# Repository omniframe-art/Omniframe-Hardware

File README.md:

**Omniframe Hardware**

Omniframe is an open source e-paper digital frame. This repository includes the source and fabrication files for the main and secondary boards for driving the [13.3" Monochrome e-ink display](https://www.eink.com/product/detail/VB3300-NCB).

Main Board includes:
* ESP32-S3 N8R2
* TPS65185
* AP61100
* BQ25505
* BQ24040
* MicroSD card slot

Secondary Board includes:
* USB Type-C Port
* Pushbutton connected to ESP GPIO

Exports include:
* Gerber files
* Assembly files
* BOM
* STEP files

The main board includes Molex 5023520-series connectors for Solar Array, Battery, and and Secondary Board. By default, connecting the main and secondary boards is done with a ribbon cable with [Molex 5023510500](https://www.digikey.com/en/products/detail/molex/5023510500/4555379) housings. Alternatively, the source files can be modified to accomodate for other connectors. 

To operate the e-paper display using this hardware, flash the [Omniframe Firmware](https://github.com/omniframe-art/Omniframe-Firmware) to the ESP. For converting and transferring images set up the [Private Image Server](https://github.com/omniframe-art/Private-Image-Server).

**Licensing**

The Omniframe framework is licensed under the terms of the [Creative Commons Attribution-ShareAlike 4.0 International License](https://creativecommons.org/licenses/by-sa/4.0/).

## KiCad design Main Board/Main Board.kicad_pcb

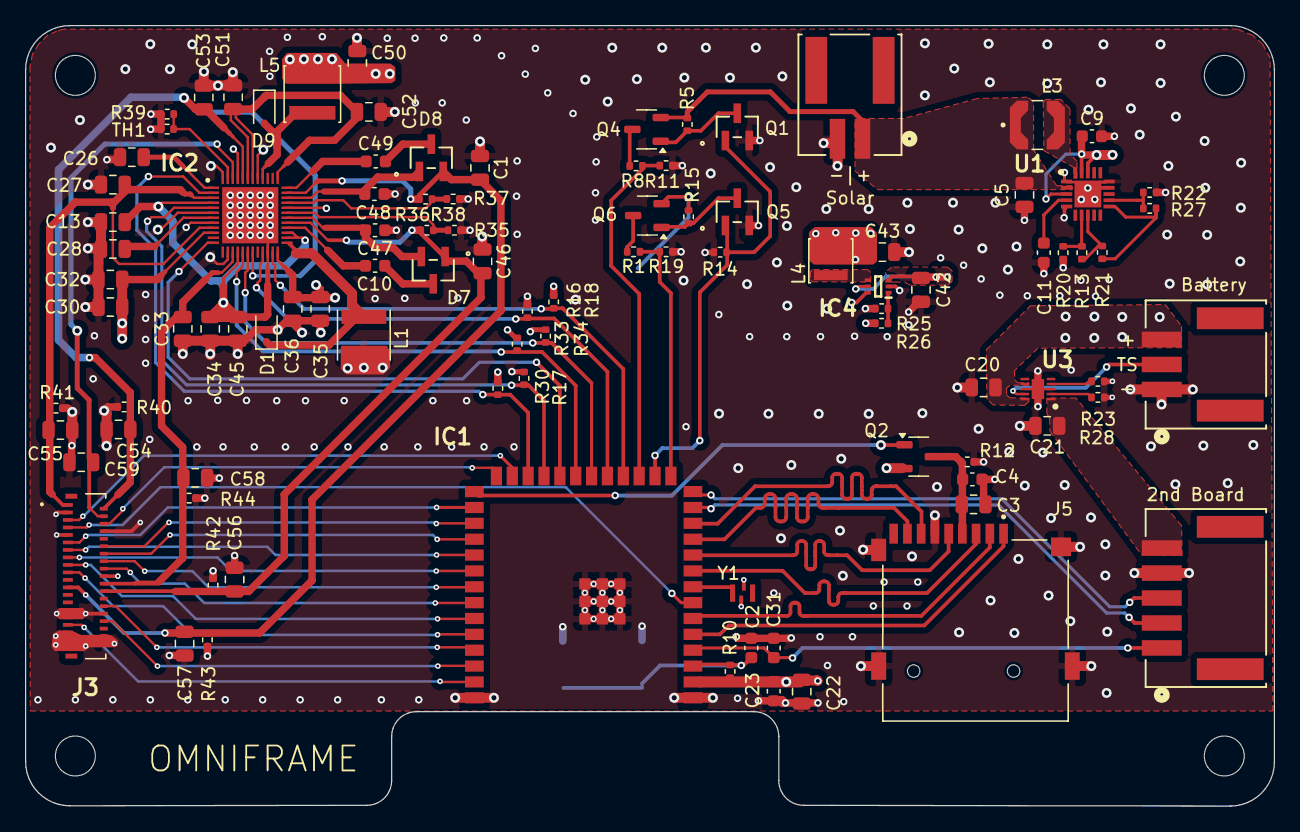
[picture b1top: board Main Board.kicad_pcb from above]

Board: 4 copper layers, 100.0 x 62.5 mm, 104 parts (1 on the bottom side), 79 nets.

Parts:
C1, C46: 2u2; C_0805_2012Metric
C2, C4, C22, C31, C47, C48: 100n; C_0603_1608Metric
C3, C23, C32, C36, C42: 22u; C_0805_2012Metric
C5, C13, C26, C27, C28, C33, C34, C45, C51, C52, C53: 4u7; C_0805_2012Metric
C9, C10, C11, C49: 10n; C_0603_1608Metric
C20, C21: 1u; C_0805_2012Metric
C30, C35, C43, C50, C59: 10u; C_0805_2012Metric
C54, C55, C58: 1uF/25V; C_0805_2012Metric
C56, C57: 1uF/50V; C_0805_2012Metric
D1, D9: BAS3010B-03W; D_SOD-323
D7, D8: BAV99,215; SOT-23TO-236_318-08_ONS-M
H1, H2, H3, H4: MountingHole; MountingHole_3.2mm_M3
IC1: ESP32-S3-WROOM-1-N8R2; ESP32S3WROOM1N8R2
IC2: TPS65185RSLT; QFN40P600X600X100-49N-D
IC4: AP61100; SOTFL50P162X60-6N
J2: 5023520300; CONN03_502352_MOL
J3: FH26W-39S-0.3SHW(60); FH26W39S03SHW60
J4: 5023520500; CONN05_502352_MOL
J5: MSD-1-A; CUI_MSD-1-A
J6: 5023520200; CONN02_502352_MOL
L1: 4.7uH 2A; L_Vishay_IFSC-1515AH_4x4x1.8mm
L3: LPS4018-223MRC; IND_LPS4018-223MRC
L4: NRH3012T1R0NN; L_Changjiang_FNR3012S
L5: 2.2uH 2A; L_Changjiang_FNR4012S
Q1, Q5: 2N7002; SOT-23TO-236_318-08_ONS-M
Q2, Q4, Q6: BSS84-7-F; SOT-23-3
R1, R5, R8, R15, R16, R17, R18, R30, R33, R34: 10k; R_0402_1005Metric
R10, R12, R14, R40, R41, R42, R43: 47k; R_0402_1005Metric
R11, R19: 30k; R_0402_1005Metric
R13: 7M32; R_0402_1005Metric
R20: 5M62; R_0402_1005Metric
R21: 1M1; R_0402_1005Metric
R22: 7M68; R_0402_1005Metric
R23: 2k; R_0402_1005Metric
R25: 44k2; R_0402_1005Metric
R26: 200k; R_0402_1005Metric
R27: 4M22; R_0402_1005Metric
R28: 590; R_0402_1005Metric
R35: 52k3; R_0402_1005Metric
R36, R38: 1M; R_0402_1005Metric
R37: 41k6; R_0402_1005Metric
R39: 43k; R_0402_1005Metric
R44: 100k; R_0402_1005Metric
S1: TS5216A 160gf 025; TS18525SL260SMTTR
TH1: 10k/3380K; R_0402_1005Metric
U1: BQ25505; QFN50P350X350X100-21N-D
U3: BQ24040DSQR; SON40P200X200X80-11N
Y1: SIT1533AC-H4-DCC-32.768E; XTAL4_SiT1533_SIT

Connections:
3V3: C22.1, C23.1, C43.1, IC1.2 (3V3), IC2.45 (VIN3P3), IC4.6 (OUT), L4.2, Q2.2 (S), R10.2, R18.2, R26.2, R30.2, R33.2, R34.2, Y1.4 (Vdd)
/15V: C53.2, C54.2, IC2.19 (VPOS_DIS), IC2.44 (VPOS), J3.2, R40.2
/22V: C1.2, C57.2, D8.2, IC2.35 (VDDH_DIS), J3.23, R38.1, R43.2
/32KP: IC1.8 (IO15), Y1.3 (CLK_Out)
/-15V: C27.1, C55.2, IC2.3 (VNEG), IC2.9 (VNEG_DIS), J3.1, R41.2
/-20V: C46.2, C56.2, D7.1, IC2.29 (VEE_DIS), J3.24, R36.1, R42.2
/BAT_VOL: IC1.15 (IO3), R1.1, R19.2
/CKV: IC1.39 (IO1), J3.33
/D0: IC1.29 (IO36), J3.12
/D1: IC1.31 (IO38), J3.13
/D2: IC1.30 (IO37), J3.14
/D3: IC1.32 (IO39), J3.15
/D4: IC1.33 (IO40), J3.16
/D5: IC1.35 (IO42), J3.17
/D6: IC1.34 (IO41), J3.18
/D7: IC1.36 (RXD0), J3.19
/EN: C2.1, IC1.3 (EN), R10.1, S1.1 (NO_1), S1.2 (NO_2)
/EPD_VDD: C59.1, IC2.46 (V3P3), J3.4
/FB: IC4.1 (FB), R25.2, R26.1
/INT_LDO: C28.2, IC2.7 (INT_LDO)
/ISET: R28.2, U3.2 (ISET)
/MODE1: IC1.37 (TXD0), J3.28
/PRE-T: R23.2, U3.4 (PRE-TERM)
/PWRUP: IC1.19 (IO11), IC2.21 (PWRUP), R16.2
/PWR_G: IC1.18 (IO10), IC2.23 (PWR_GOOD), R18.1
/SCL: IC1.21 (IO13), IC2.17 (SCL), R33.1
/SDA: IC1.20 (IO12), IC2.18 (SDA), R34.1
/SD_CLK: IC1.10 (IO17), J5.5 (CLK)
/SD_CMD: IC1.9 (IO16), J5.3 (CMD)
/SD_D0: IC1.12 (IO8), J5.7 (DAT0)
/SD_D1: IC1.11 (IO18), J5.8 (DAT1)
/SD_D2: IC1.5 (IO5), J5.1 (DAT2)
/SD_D3: IC1.6 (IO6), J5.2 (CD/DAT3)
/SD_EN: IC1.27 (IO0), Q2.1 (G)
/SIG: C31.1, IC1.4 (IO4), J4.1
/SOL+: C5.1, J6.1, L3.1, Q4.2 (S), R5.2, U1.2 (VIN_DC)
/SOL_VOL: IC1.17 (IO9), R8.1, R11.2
/SPV: IC1.38 (IO2), J3.32
/SW: IC4.4 (SW), L4.1
/TS: J2.2, U3.9 (TS)
/USB_N: IC1.13 (IO19), J4.2
/USB_P: IC1.14 (IO20), J4.3
/VBAT: C9.1, C20.1, C30.1, C32.2, C35.1, C36.2, C42.1, C50.1, IC2.10 (VIN), IC2.24 (VIN_P), IC4.3 (VIN), IC4.5 (EN), J2.3, L5.2, Q6.2 (S), R15.2, U1.3 (VOC_SAMP), U1.18 (VBAT_SEC), U1.19 (VSTOR), U3.7 (ISET2), U3.10 (OUT)
/VBUS: C21.1, J4.5, U3.1 (IN)
/VCOM: C33.2, C58.2, IC2.15 (VCOM), J3.22, R44.2
/VCTRL: IC1.22 (IO14), IC2.12 (VCOM_CTRL)
/VDDH_D: C48.1, D8.1, IC2.34 (VDDH_D)
/VDDH_DRV: C49.1, IC2.36 (VDDH_DRV)
/VDDH_FB: IC2.33 (VDDH_FB), R37.2, R38.2
/VEE_D: C47.2, D7.2, IC2.30 (VEE_D)
/VEE_DRV: C10.1, IC2.28 (VEE_DRV)
/VEE_FB: IC2.31 (VEE_FB), R35.2, R36.2
/VNEG_IN: C13.1, C34.1, C45.2, D1.2 (A), IC2.4 (VNEG_IN), IC2.16 (VCOM_PWR), IC2.22 (PBKG), IC2.26 (VN), IC2.27 (VEE_IN), IC2.49 (EP)
/VN_SW: D1.1 (K), IC2.25 (VN_SW), L1.1
/VOL_EN: IC1.16 (IO46), Q1.1 (G), Q5.1 (G), R14.2
/VREF: C26.2, IC2.1 (VREF)
/WKUP: IC1.23 (IO21), IC2.5 (WAKEUP), R17.2
/XCL: IC1.25 (IO48), J3.5
/XLE: IC1.26 (IO45), J3.6
/XOE: IC1.7 (IO7), J3.7
/XSTL: IC1.28 (IO35), J3.11
/nINT: IC1.24 (IO47), IC2.2 (~INT), R30.1
GND: C1.1, C2.2, C3.2, C4.2, C5.2, C9.2, C11.2, C13.2, C20.2, C21.2, C22.2, C23.2, C26.1, C27.2, C28.1, C30.2, C31.2, C32.1, C33.1, C34.2, C35.2, C36.1, C42.2, C43.2, C45.1, C46.1, C47.1, C48.2, C50.2, C51.1, C52.1, C53.1, C54.1, C55.1, C56.1, C57.1, C58.1, C59.2, IC1.1 (GND_1), IC1.40 (GND_2), IC1.41 (GND_3), IC1.42 (GND_4), IC1.43 (GND_5), IC1.44 (GND_6), IC1.45 (GND_7), IC1.46 (GND_8), IC1.47 (GND_9), IC1.48 (GND_10), IC1.49 (GND_11), IC2.6 (DGND), IC2.8 (AGND1), IC2.14 (VCOM_DIS), IC2.32 (PGND2), IC2.41 (PGND1), IC2.48 (AGND2), IC4.2 (GND), J2.1, J3.3, J3.8, J3.9, J3.20, J3.29, J3.30, J3.31, J3.35, J3.36, J3.37, J3.38, J3.39, J4.4, J5.6 (VSS), J5.G1 (COVER_GND), J5.G2 (COVER_GND__1), J5.G3 (COVER_GND__2), J5.G4 (COVER_GND__3), J6.2, L1.2, Q1.2 (S), Q5.2 (S), R11.1, R12.1, R14.1, R16.1, R17.1, R19.1, R20.1, R23.1, R25.1, R27.1, R28.1, R35.1, R37.1, R39.2, R40.1, R41.1, R42.1, R43.1, R44.1, S1.3 (COM_1), S1.4 (COM_2), TH1.1, U1.1 (VSS), U1.5 (~EN), U1.14 (VBAT_PRI), U1.15 (VSS), U3.3 (VSS), U3.8 (~CHG), U3.11 (EP), Y1.2 (GND)
unnamed: C10.2, D7.3
unnamed: C49.2, D8.3
unnamed: D9.2 (A), IC2.40 (VB_SW), L5.1
unnamed: C51.2, C52.2, D9.1 (K), IC2.37 (VDDH_IN), IC2.42 (VB), IC2.43 (VPOS_IN)
unnamed: IC2.47 (TS), R39.1, TH1.2
unnamed: C3.1, C4.1, J5.4 (VDD), Q2.3 (D), R12.2
unnamed: Q1.3 (D), Q4.1 (G), R5.1
unnamed: Q4.3 (D), R8.2
unnamed: Q5.3 (D), Q6.1 (G), R15.1
unnamed: Q6.3 (D), R1.2
unnamed: L3.2, U1.20 (LBOOST)
unnamed: R21.1, R22.2, U1.11 (OK_HYST)
unnamed: R22.1, R27.2, U1.12 (OK_PROG)
unnamed: R13.1, R20.2, U1.7 (VBAT_OV)
unnamed: R13.2, R21.2, U1.8 (VRDIV)
unnamed: C11.1, U1.4 (VREF_SAMP)

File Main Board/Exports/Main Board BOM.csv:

"Reference","Value","Footprint","Qty","DNP","Description"
"C1,C46","2u2","Capacitor_SMD:C_0805_2012Metric","2","","Capacitor"
"C2,C4,C22,C31,C47,C48","100n","Capacitor_SMD:C_0603_1608Metric","6","",""
"C3,C23,C32,C36,C42","22u","Capacitor_SMD:C_0805_2012Metric","5","",""
"C5,C13,C26,C27,C28,C33,C34,C45,C51,C52,C53","4u7","Capacitor_SMD:C_0805_2012Metric","11","",""
"C9,C10,C11,C49","10n","Capacitor_SMD:C_0603_1608Metric","4","",""
"C20,C21","1u","Capacitor_SMD:C_0805_2012Metric","2","",""
"C30,C35,C43,C50,C59","10u","Capacitor_SMD:C_0805_2012Metric","5","",""
"C54,C55,C58","1uF/25V","Capacitor_SMD:C_0805_2012Metric","3","",""
"C56,C57","1uF/50V","Capacitor_SMD:C_0805_2012Metric","2","",""
"D1,D9","BAS3010B-03W","Diode_SMD:D_SOD-323","2","",""
"D7,D8","BAV99,215","Libraries:SOT-23TO-236_318-08_ONS-M","2","",""
"H1,H2,H3,H4","MountingHole","MountingHole:MountingHole_3.2mm_M3","4","",""
"IC1","ESP32-S3-WROOM-1-N8R2","ESP:ESP32S3WROOM1N8R2","1","","WiFi Modules - 802.11 (Engineering Samples Only) SMD Module, ESP32-S3R2, 2 MB PSRAM, 8 MB SPI Flash, PCB Antenna ,,"
"IC2","TPS65185RSLT","TPS65185:QFN40P600X600X100-49N-D","1","","Power Management Specialised - PMIC PMIC FOR E-INK PAPER DISPLAY"
"IC4","AP61100","AP61300:SOTFL50P162X60-6N","1","","DCDC Conv LV Buck SOT563 T&R 3K"
"J2","5023520300","5023520300:CONN03_502352_MOL","1","",""
"J3","FH26W-39S-0.3SHW(60)","Libraries:FH26W39S03SHW60","1","",""
"J4","5023520500","5023520500:CONN05_502352_MOL","1","",""
"J5","MSD-1-A","MSD-1-A:CUI_MSD-1-A","1","",""
"J6","5023520200","5023520200:CONN02_502352_MOL","1","",""
"L1","4.7uH 2A","Inductor_SMD:L_Vishay_IFSC-1515AH_4x4x1.8mm","1","",""
"L3","LPS4018-223MRC","LPS4018_223MRC:IND_LPS4018-223MRC","1","",""
"L4","NRH3012T1R0NN","Inductor_SMD:L_Changjiang_FNR3012S","1","",""
"L5","2.2uH 2A","Inductor_SMD:L_Changjiang_FNR4012S","1","","Inductor"
"Q1,Q5","2N7002","Libraries:SOT-23TO-236_318-08_ONS-M","2","","N-MOSFET transistor, drain/source/gate"
"Q2,Q4,Q6","BSS84-7-F","Package_TO_SOT_SMD:SOT-23-3","3","","P-MOSFET transistor, drain/source/gate"
"R1,R5,R8,R15,R16,R17,R18,R30,R33,R34","10k","Resistor_SMD:R_0402_1005Metric","10","",""
"R10,R12,R14,R40,R41,R42,R43","47k","Resistor_SMD:R_0402_1005Metric","7","",""
"R11,R19","30k","Resistor_SMD:R_0402_1005Metric","2","",""
"R13","7M32","Resistor_SMD:R_0402_1005Metric","1","",""
"R20","5M62","Resistor_SMD:R_0402_1005Metric","1","",""
"R21","1M1","Resistor_SMD:R_0402_1005Metric","1","",""
"R22","7M68","Resistor_SMD:R_0402_1005Metric","1","",""
"R23","2k","Resistor_SMD:R_0402_1005Metric","1","",""
"R25","44k2","Resistor_SMD:R_0402_1005Metric","1","",""
"R26","200k","Resistor_SMD:R_0402_1005Metric","1","",""
"R27","4M22","Resistor_SMD:R_0402_1005Metric","1","",""
"R28","590","Resistor_SMD:R_0402_1005Metric","1","",""
"R35","52k3","Resistor_SMD:R_0402_1005Metric","1","",""
"R36,R38","1M","Resistor_SMD:R_0402_1005Metric","2","",""
"R37","41k6","Resistor_SMD:R_0402_1005Metric","1","",""
"R39","43k","Resistor_SMD:R_0402_1005Metric","1","",""
"R44","100k","Resistor_SMD:R_0402_1005Metric","1","",""
"S1","TS5216A 160gf 025","TS18-5-25-SL-260-SMT-TR:TS18525SL260SMTTR","1","","None Without 50mA 5.2mm 100MΩ 100000 Times 12V 160gf 5.2mm 1.6mm Round Button Standing paste SPST SMD-4P,5.2x5.2mm Tactile Switches ROHS"
"TH1","10k/3380K","Resistor_SMD:R_0402_1005Metric","1","",""
"U1","BQ25505","bq25505:QFN50P350X350X100-21N-D","1","","Nano Power Boost Charger and Buck Converter for Energy Harvester Powered Applications, QFN-20"
"U3","BQ24040DSQR","BQ24040:SON40P200X200X80-11N","1","",""
"Y1","SIT1533AC-H4-DCC-32.768E","Libraries:XTAL4_SiT1533_SIT","1","",""

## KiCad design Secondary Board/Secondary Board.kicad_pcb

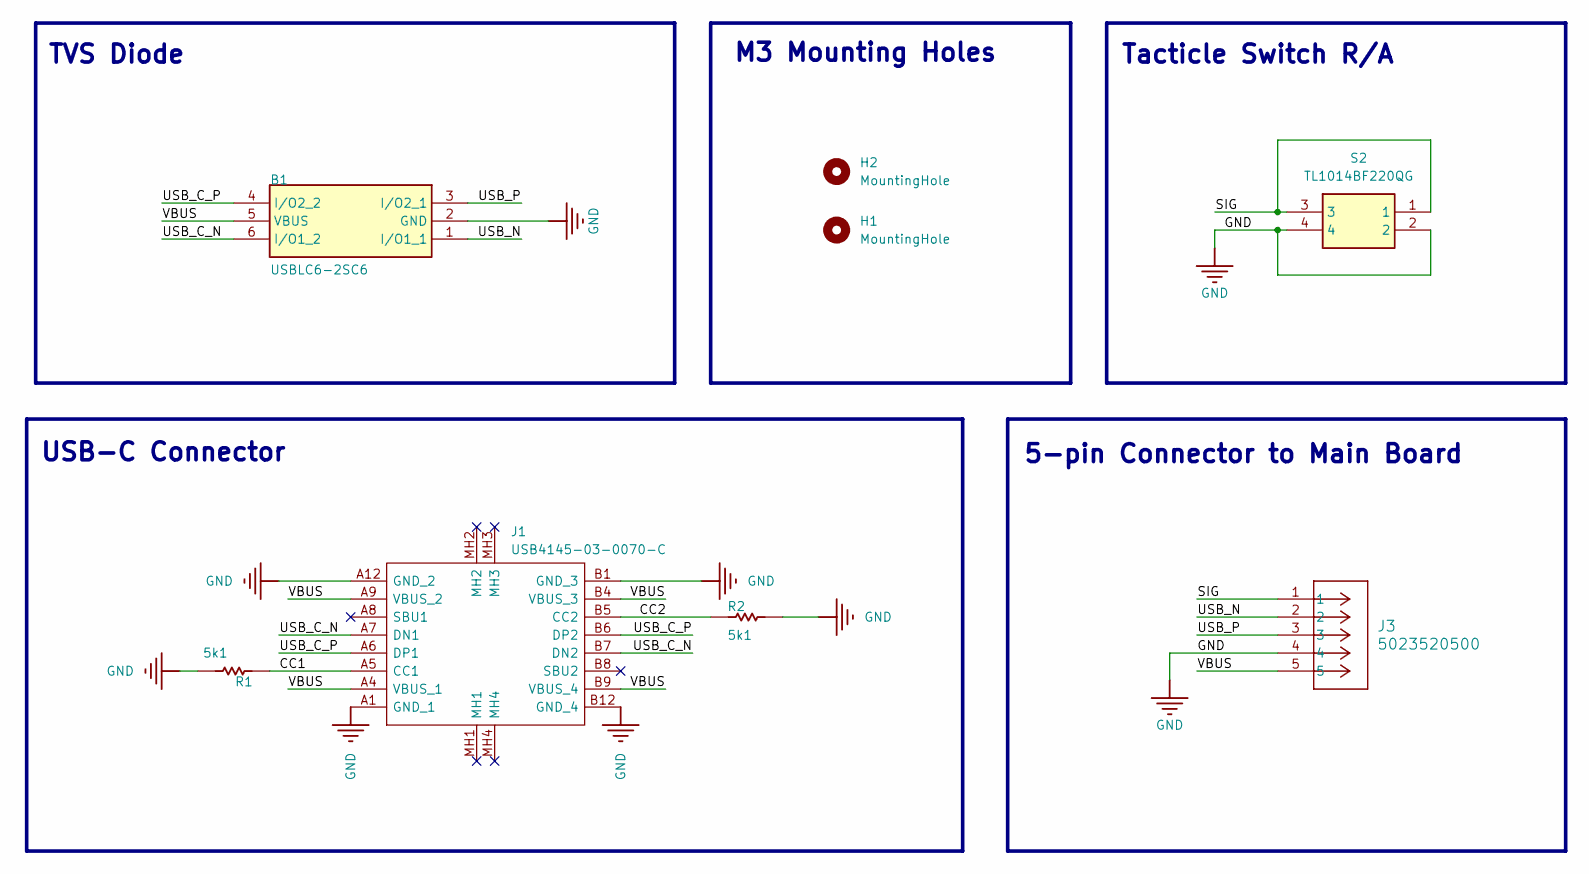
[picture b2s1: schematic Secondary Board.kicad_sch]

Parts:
B1: USBLC6-2SC6; SOT-23-6; MOUSER PART NUMBER 511-USBLC6-2SC6
H1, H2: MountingHole; MountingHole_3.2mm_M3
J1: USB4145-03-0070-C; USB4145030070C; Mouser Part Number 640-USB4145-3-0070-C
J3: 5023520500; CONN05_502352_MOL
R1, R2: 5k1; R_0402_1005Metric; PART NUMBER RC0402FR-075K1L
S2: TL1014BF220QG; Mouser Part Number 612-TL1014BF220QG

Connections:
/CC1: J1.A5 (CC1), R1.1
/CC2: J1.B5 (CC2), R2.1
/SIG: J3.1, S2.1, S2.3
/USB_C_N: B1.6 (I/O1_2), J1.A7 (DN1), J1.B7 (DN2)
/USB_C_P: B1.4 (I/O2_2), J1.A6 (DP1), J1.B6 (DP2)
/USB_N: B1.1 (I/O1_1), J3.2
/USB_P: B1.3 (I/O2_1), J3.3
/VBUS: B1.5 (VBUS), J1.A4 (VBUS_1), J1.A9 (VBUS_2), J1.B4 (VBUS_3), J1.B9 (VBUS_4), J3.5
GND: B1.2 (GND), J1.A1 (GND_1), J1.A12 (GND_2), J1.B1 (GND_3), J1.B12 (GND_4), J3.4, R1.2, R2.2, S2.2, S2.4

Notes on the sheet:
Tacticle Switch R/A
5-pin Connector to Main Board
USB-C Connector
TVS Diode
M3 Mounting Holes

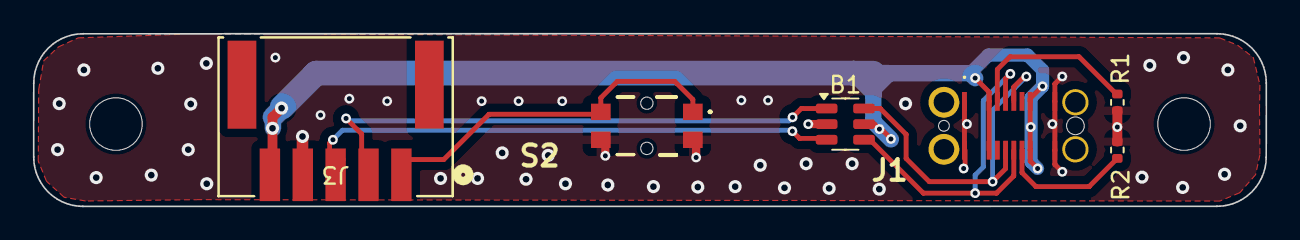
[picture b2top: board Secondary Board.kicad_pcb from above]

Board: 2 copper layers, 75.0 x 10.5 mm, 8 parts (0 on the bottom side), 9 nets.

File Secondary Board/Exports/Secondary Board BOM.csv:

"Id";"Designator";"Footprint";"Quantity";"Designation";"Supplier and ref";
1;"J3";"CONN05_502352_MOL";1;"5023520500";;;
2;"R2,R1";"R_0402_1005Metric";2;"5k1";;;
3;"J1";"USB4145030070C";1;"USB4145-03-0070-C";;;
4;"S2";"TL1014BF220QG";1;"TL1014BF220QG";;;
5;"B1";"SOT-23-6";1;"USBLC6-2SC6";;;

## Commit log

2025-06-09 Add .gitignore for macOS system files
2025-06-09 Remove .DS_Store from tracking
2025-06-09 Clean up README formatting
2025-06-09 Remove .DS_Store files from tracking
2025-06-10 Updated 3D-file
2025-06-12 fix silkscreen
